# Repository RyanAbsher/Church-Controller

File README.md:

# Church-Controller
Controller for Church Status Signs

## Introduction
After I finished the [status signs](https://github.com/RyanAbsher/Church-Sign/) for my church, the only way I had to control them was using POST links from a document on my phone.
If I was not attending on a given day, then no one else could use them.
I decided to make a hand-held control, similar to a television remote control, that was simple enough for anyone to pick up and use.

## Hardware
The core of the controller is an ESP-12e module. There are 3 LEDs the match the color options for the status signs, Green, Yellow, and Red.
There are 2 buttons which will be labelled Change and Save. Pressing the Change button will cycle through the 3 LEDs. Once you are on the correct color
press the Save button to send the change to the status signs. All connected signs will change to the same color.
The controller is powered by 3 standard replaceable AA batteries. There is also a low battery indicator LED on the front of the controller.

The hardware was designed using KiCAD. As this was a one-off device, I decided to etch my own 2 sided board instead of ordering from a low cost PCB manufacturer.
This will also allow me to rapidly iterate through designs of there are any mistakes.

## Software
The controller, just like the status signs, is programmed using the Arduino IDE. The status signs publish their Hostname and IP using mDNS. When first powered on, the controller
will search the local network for any such signs. It will perform a connection test with each sign and store the connected devices for future use. If no signs are located, the controller
will use it's LEDs to indicate an error status.

## Case
The case was designed in Fusion 360, and printed in ABS with a standard desktop FDM printer.

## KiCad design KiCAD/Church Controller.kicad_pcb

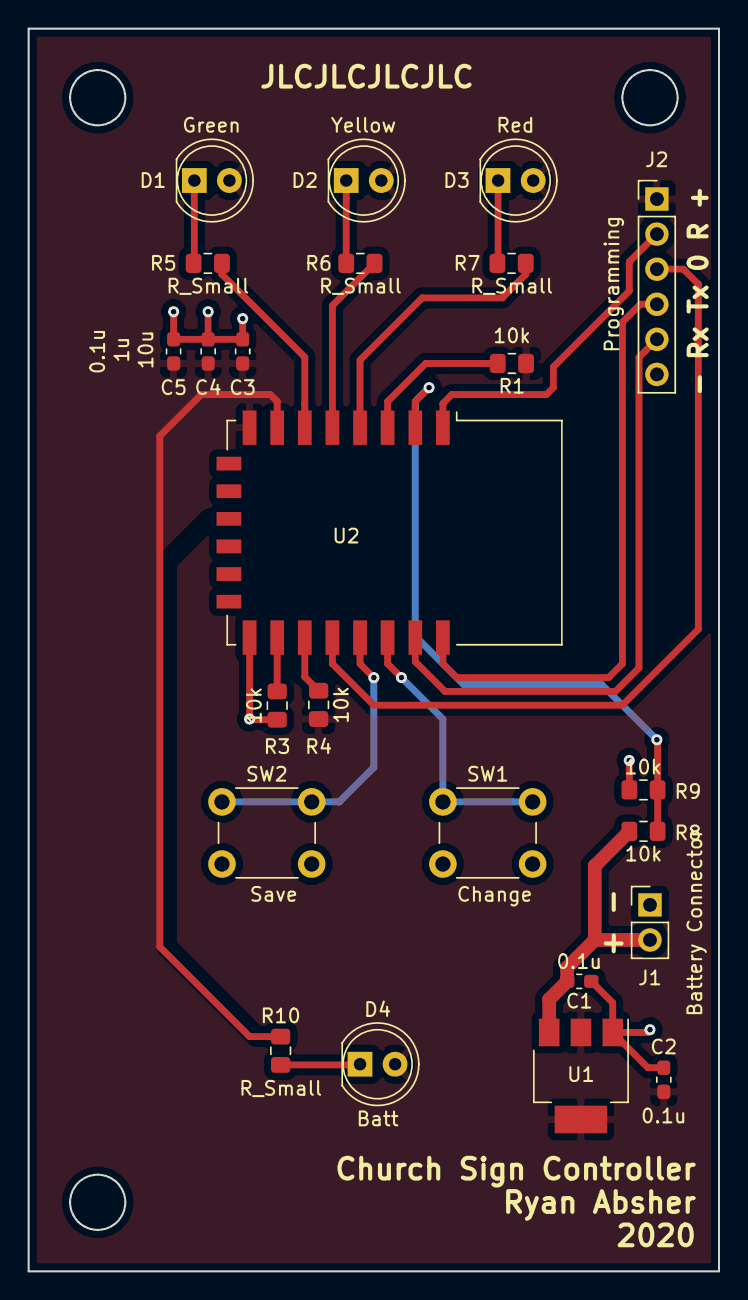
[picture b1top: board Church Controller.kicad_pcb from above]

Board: 2 copper layers, 50.0 x 90.0 mm, 24 parts (0 on the bottom side), 21 nets.

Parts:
C1, C2, C5: 0.1u; C_0603_1608Metric_Pad1.05x0.95mm_HandSolder
C3: 10u; C_0603_1608Metric_Pad1.05x0.95mm_HandSolder
C4: 1u; C_0603_1608Metric_Pad1.05x0.95mm_HandSolder
D1: Green; LED_D5.0mm
D2: Yellow; LED_D5.0mm
D3: Red; LED_D5.0mm
D4: Batt; LED_D5.0mm
J1: Battery Connector; PinHeader_1x02_P2.54mm_Vertical
J2: Programming; PinHeader_1x06_P2.54mm_Vertical
R1, R3, R4, R8, R9: 10k; R_0805_2012Metric_Pad1.15x1.40mm_HandSolder
R5, R6, R7, R10: R_Small; R_0805_2012Metric_Pad1.15x1.40mm_HandSolder
SW1: Change; SW_PUSH_6mm_H9.5mm
SW2: Save; SW_PUSH_6mm_H9.5mm
U1: AZ1117-3.3; SOT-223-3_TabPin2
U2: ESP-12E

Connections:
+3V3: C2.2, C3.2, C4.2, C5.2, D1.2, D2.2, D3.2, D4.2, J2.1, R1.1, R4.1, U1.2, U2.8
/BUTTON_CHANGE: SW1.1, U2.20
/BUTTON_SAVE: SW2.1, U2.19
/GPIO0: J2.3, U2.18
/LED_BATT: R10.2, U2.7
/LED_GREEN: R5.2, U2.6
/LED_RED: R7.2, U2.4
/LED_YELLOW: R6.2, U2.5
/Rx: J2.5, U2.21
/Tx: J2.4, U2.22
/~RST: J2.2, U2.1
GND: C1.1, C2.1, C3.1, C4.1, C5.1, J1.1, J2.6, R3.2, R9.2, SW1.2, SW2.2, U1.1, U2.15
unnamed: D1.1, R5.1
unnamed: D2.1, R6.1
unnamed: D3.1, R7.1
unnamed: D4.1, R10.1
unnamed: R1.2, U2.3
unnamed: R3.1, U2.16
unnamed: R4.2, U2.17
unnamed: R8.2, R9.1, U2.2
VCC: C1.2, J1.2, R8.1, U1.3

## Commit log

2020-07-22 Update and Corrections
    Centered some misplaced components, added registration / screw holes to PCB.
2020-07-23 Update
    I made the pads for the programming header solid for use with a pogo pin programmer.
2020-07-24 Reorganization
    I reorganized the directory structure to allow for the Arduino code.
2020-07-29 Update
    Organized schematic
2020-08-07 Update
    Changed programming header, organized silkscreen, generated gerbers, added one missing trace.
2020-08-07 Updated schematic to match last PCB update
2020-08-15 Correction
    I didn't realize that you couldn't use GPIO 9 on the ESP-12e. Moved battery LED to GPIO 13.
